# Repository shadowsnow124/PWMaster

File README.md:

# PWMaster

**PWMaster** is a dedicated controller designed for the **PWBus** system, built to operate seamlessly with **Buck**, **Boost**, and **Buck-Boost** power converters. The entire system is engineered under core principles of **simplicity** and **minimalist component design**, ensuring ease of understanding, implementation, and reduced hardware complexity.

---

## Key Features

* **Multi-Topology Support:** Compatible with three fundamental power converter configurations:
  * **Buck Converter** (Step-Down)
  * **Boost Converter** (Step-Up)
  * **Buck-Boost Converter** (Step-Up/Step-Down)
* **Simplicity & Minimalism:** Features an uncomplicated control structure that significantly reduces the overall component count in hardware designs.
* **Cost-Effective & Efficient:** Lower component requirements translate to reduced production costs while maintaining robust stability and control over the PWBus architecture.

---

## Getting Started

### Prerequisites
* PWBus-compatible hardware (Buck, Boost, or Buck-Boost Converter circuit)
* Appropriate IDE or toolchain for compilation and flashing

## Contributing

Contributions are always welcome! If you have suggestions, feature requests, or bug reports, please feel free to open an issue or submit a pull request.

---

## License

This project is licensed under the [GPL3.0 License](LICENSE).

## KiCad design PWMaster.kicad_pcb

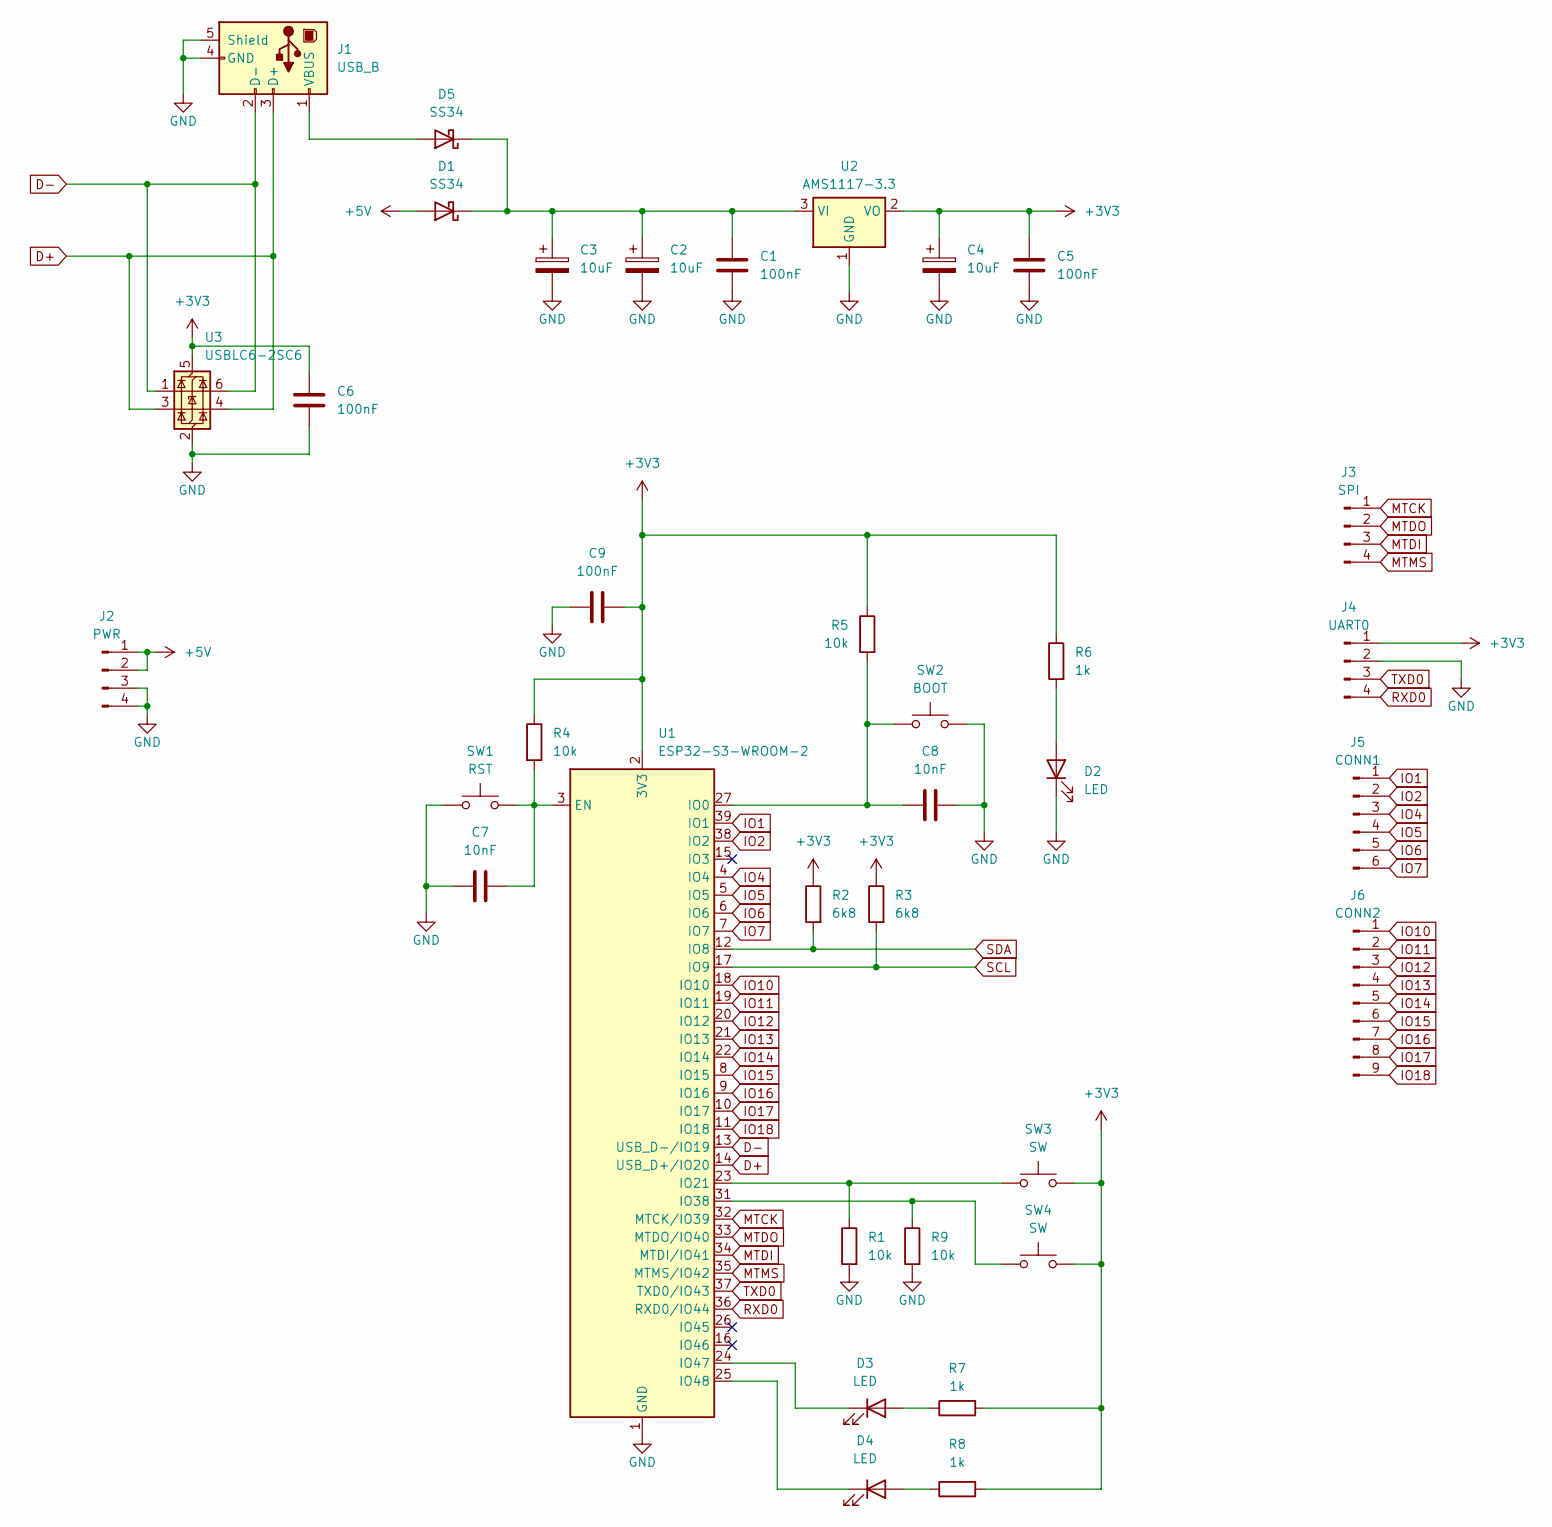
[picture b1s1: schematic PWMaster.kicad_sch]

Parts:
C1, C5, C6, C9: 100nF; C_0805_2012Metric
C2, C3, C4: 10uF; CP_Radial_D5.0mm_P2.00mm
C7, C8: 10nF; C_0805_2012Metric
D1, D5: SS34; D_SMA
D2, D3, D4: LED; LED_D3.0mm
J1: USB_B; USB_B_OST_USB-B1HSxx_Horizontal
J2: PWR; PinHeader_1x04_P2.54mm_Vertical
J3: SPI; PinHeader_1x04_P2.54mm_Vertical
J4: UART0; PinHeader_1x04_P2.54mm_Vertical
J5: CONN1; PinHeader_1x06_P2.54mm_Vertical
J6: CONN2; PinHeader_1x09_P2.54mm_Vertical
R1, R4, R5, R9: 10k; R_0805_2012Metric
R2, R3: 6k8; R_0805_2012Metric
R6, R7, R8: 1k; R_0805_2012Metric
SW1: RST; SW_PUSH_6mm
SW2: BOOT; SW_PUSH_6mm
SW3, SW4: SW; SW_PUSH_6mm
U1: ESP32-S3-WROOM-2
U2: AMS1117-3.3; SOT-223-3_TabPin2
U3: USBLC6-2SC6; SOT-23-6

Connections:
+3V3: C4.1, C5.1, C6.1, C9.1, J4.1, R2.1, R3.1, R4.1, R5.1, R6.1, R7.2, R8.2, SW3.1, SW4.1, U1.2 (3V3), U2.2 (VO), U3.5 (VBUS)
+5V: D1.2 (A), J2.1, J2.2
D+: J1.3 (D+), U1.14 (USB_D+/IO20), U3.3 (I/O2), U3.4 (I/O2)
D-: J1.2 (D-), U1.13 (USB_D-/IO19), U3.1 (I/O1), U3.6 (I/O1)
GND: C1.2, C2.2, C3.2, C4.2, C5.2, C6.2, C7.1, C8.1, C9.2, D2.1 (K), J1.4 (GND), J1.5 (Shield), J2.3, J2.4, J4.2, R1.2, R9.2, SW1.1, SW2.1, U1.1 (GND), U1.40 (GND), U1.41 (GND), U2.1 (GND), U3.2 (GND)
IO1: J5.1, U1.39 (IO1)
IO2: J5.2, U1.38 (IO2)
IO4: J5.3, U1.4 (IO4)
IO5: J5.4, U1.5 (IO5)
IO6: J5.5, U1.6 (IO6)
IO7: J5.6, U1.7 (IO7)
IO10: J6.1, U1.18 (IO10)
IO11: J6.2, U1.19 (IO11)
IO12: J6.3, U1.20 (IO12)
IO13: J6.4, U1.21 (IO13)
IO14: J6.5, U1.22 (IO14)
IO15: J6.6, U1.8 (IO15)
IO16: J6.7, U1.9 (IO16)
IO17: J6.8, U1.10 (IO17)
IO18: J6.9, U1.11 (IO18)
MTCK: J3.1, U1.32 (MTCK/IO39)
MTDI: J3.3, U1.34 (MTDI/IO41)
MTDO: J3.2, U1.33 (MTDO/IO40)
MTMS: J3.4, U1.35 (MTMS/IO42)
unnamed: C1.1, C2.1, C3.1, D1.1 (K), D5.1 (K), U2.3 (VI)
unnamed: D2.2 (A), R6.2
unnamed: D3.2 (A), R7.1
unnamed: D3.1 (K), U1.24 (IO47)
unnamed: D4.2 (A), R8.1
unnamed: D4.1 (K), U1.25 (IO48)
unnamed: D5.2 (A), J1.1 (VBUS)
unnamed: C7.2, R4.2, SW1.2, U1.3 (EN)
unnamed: C8.2, R5.2, SW2.2, U1.27 (IO0)
unnamed: R1.1, SW3.2, U1.23 (IO21)
unnamed: R9.1, SW4.2, U1.31 (IO38)
RXD0: J4.4, U1.36 (RXD0/IO44)
SCL: R3.2, U1.17 (IO9)
SDA: R2.2, U1.12 (IO8)
TXD0: J4.3, U1.37 (TXD0/IO43)

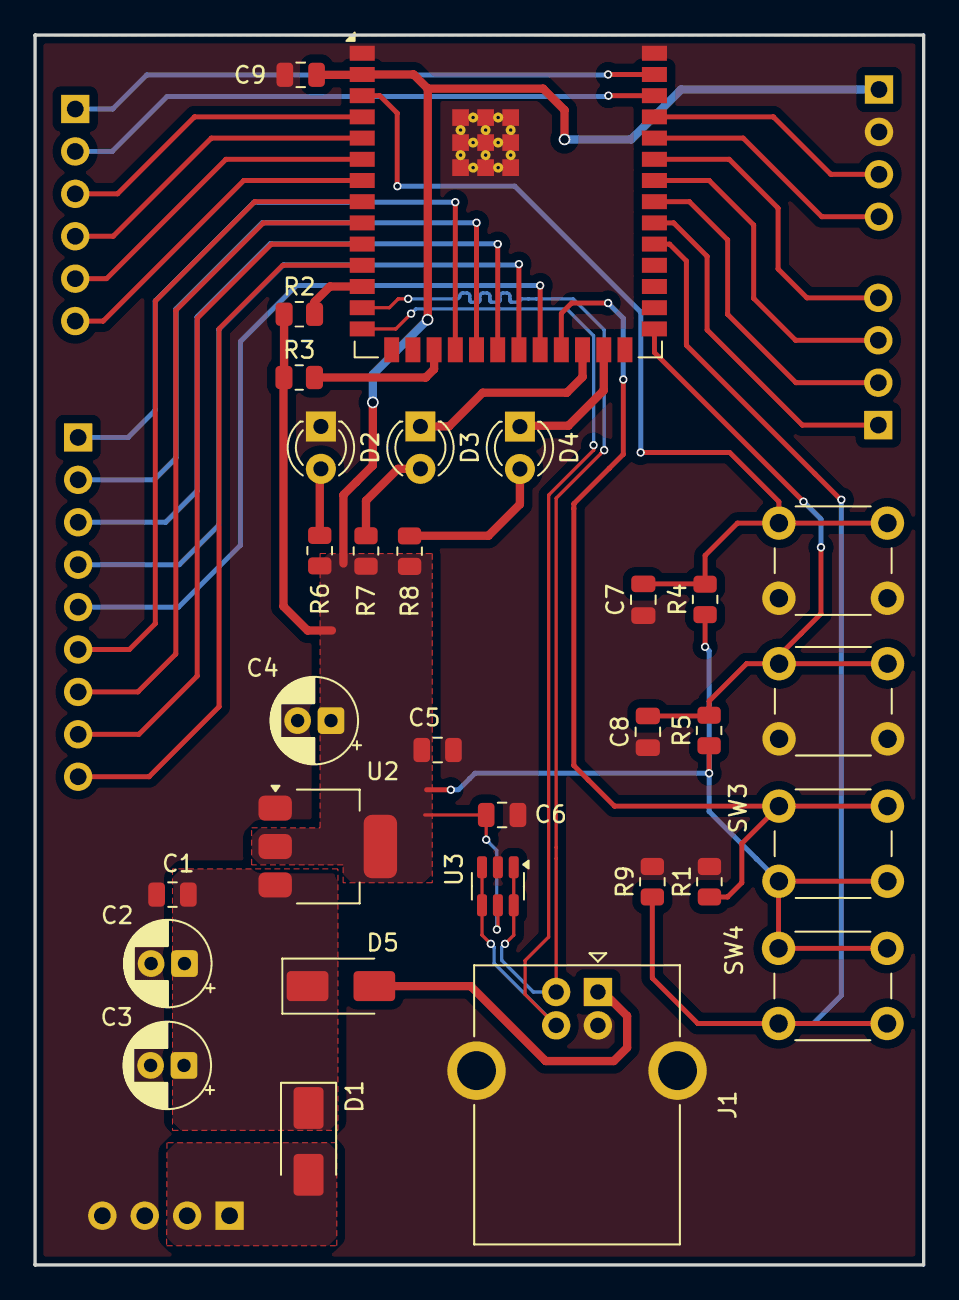
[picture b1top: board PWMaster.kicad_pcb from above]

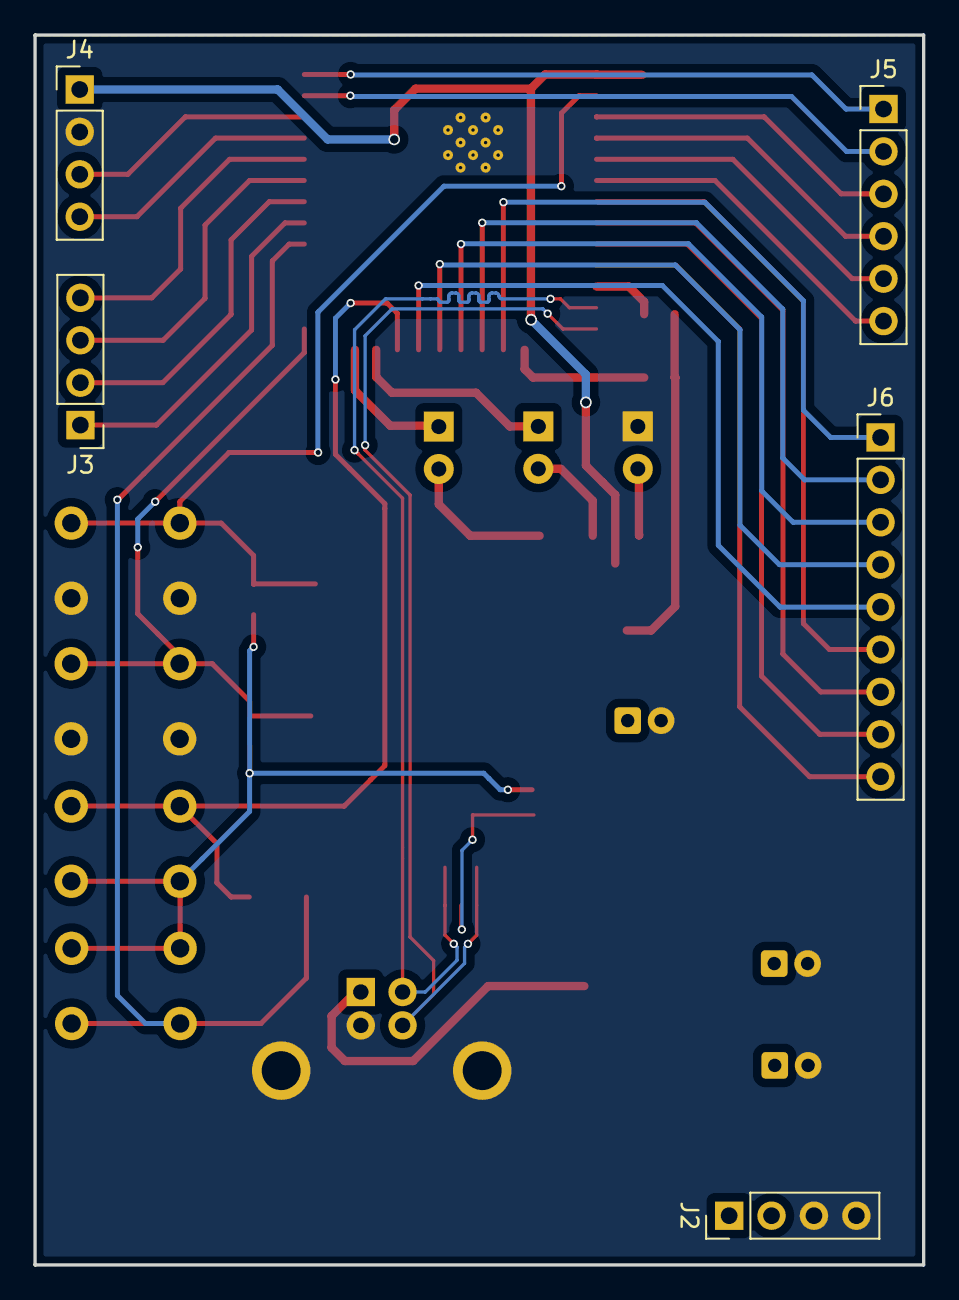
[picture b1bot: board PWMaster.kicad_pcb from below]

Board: 2 copper layers, 53.2 x 73.7 mm, 36 parts (5 on the bottom side), 39 nets.
